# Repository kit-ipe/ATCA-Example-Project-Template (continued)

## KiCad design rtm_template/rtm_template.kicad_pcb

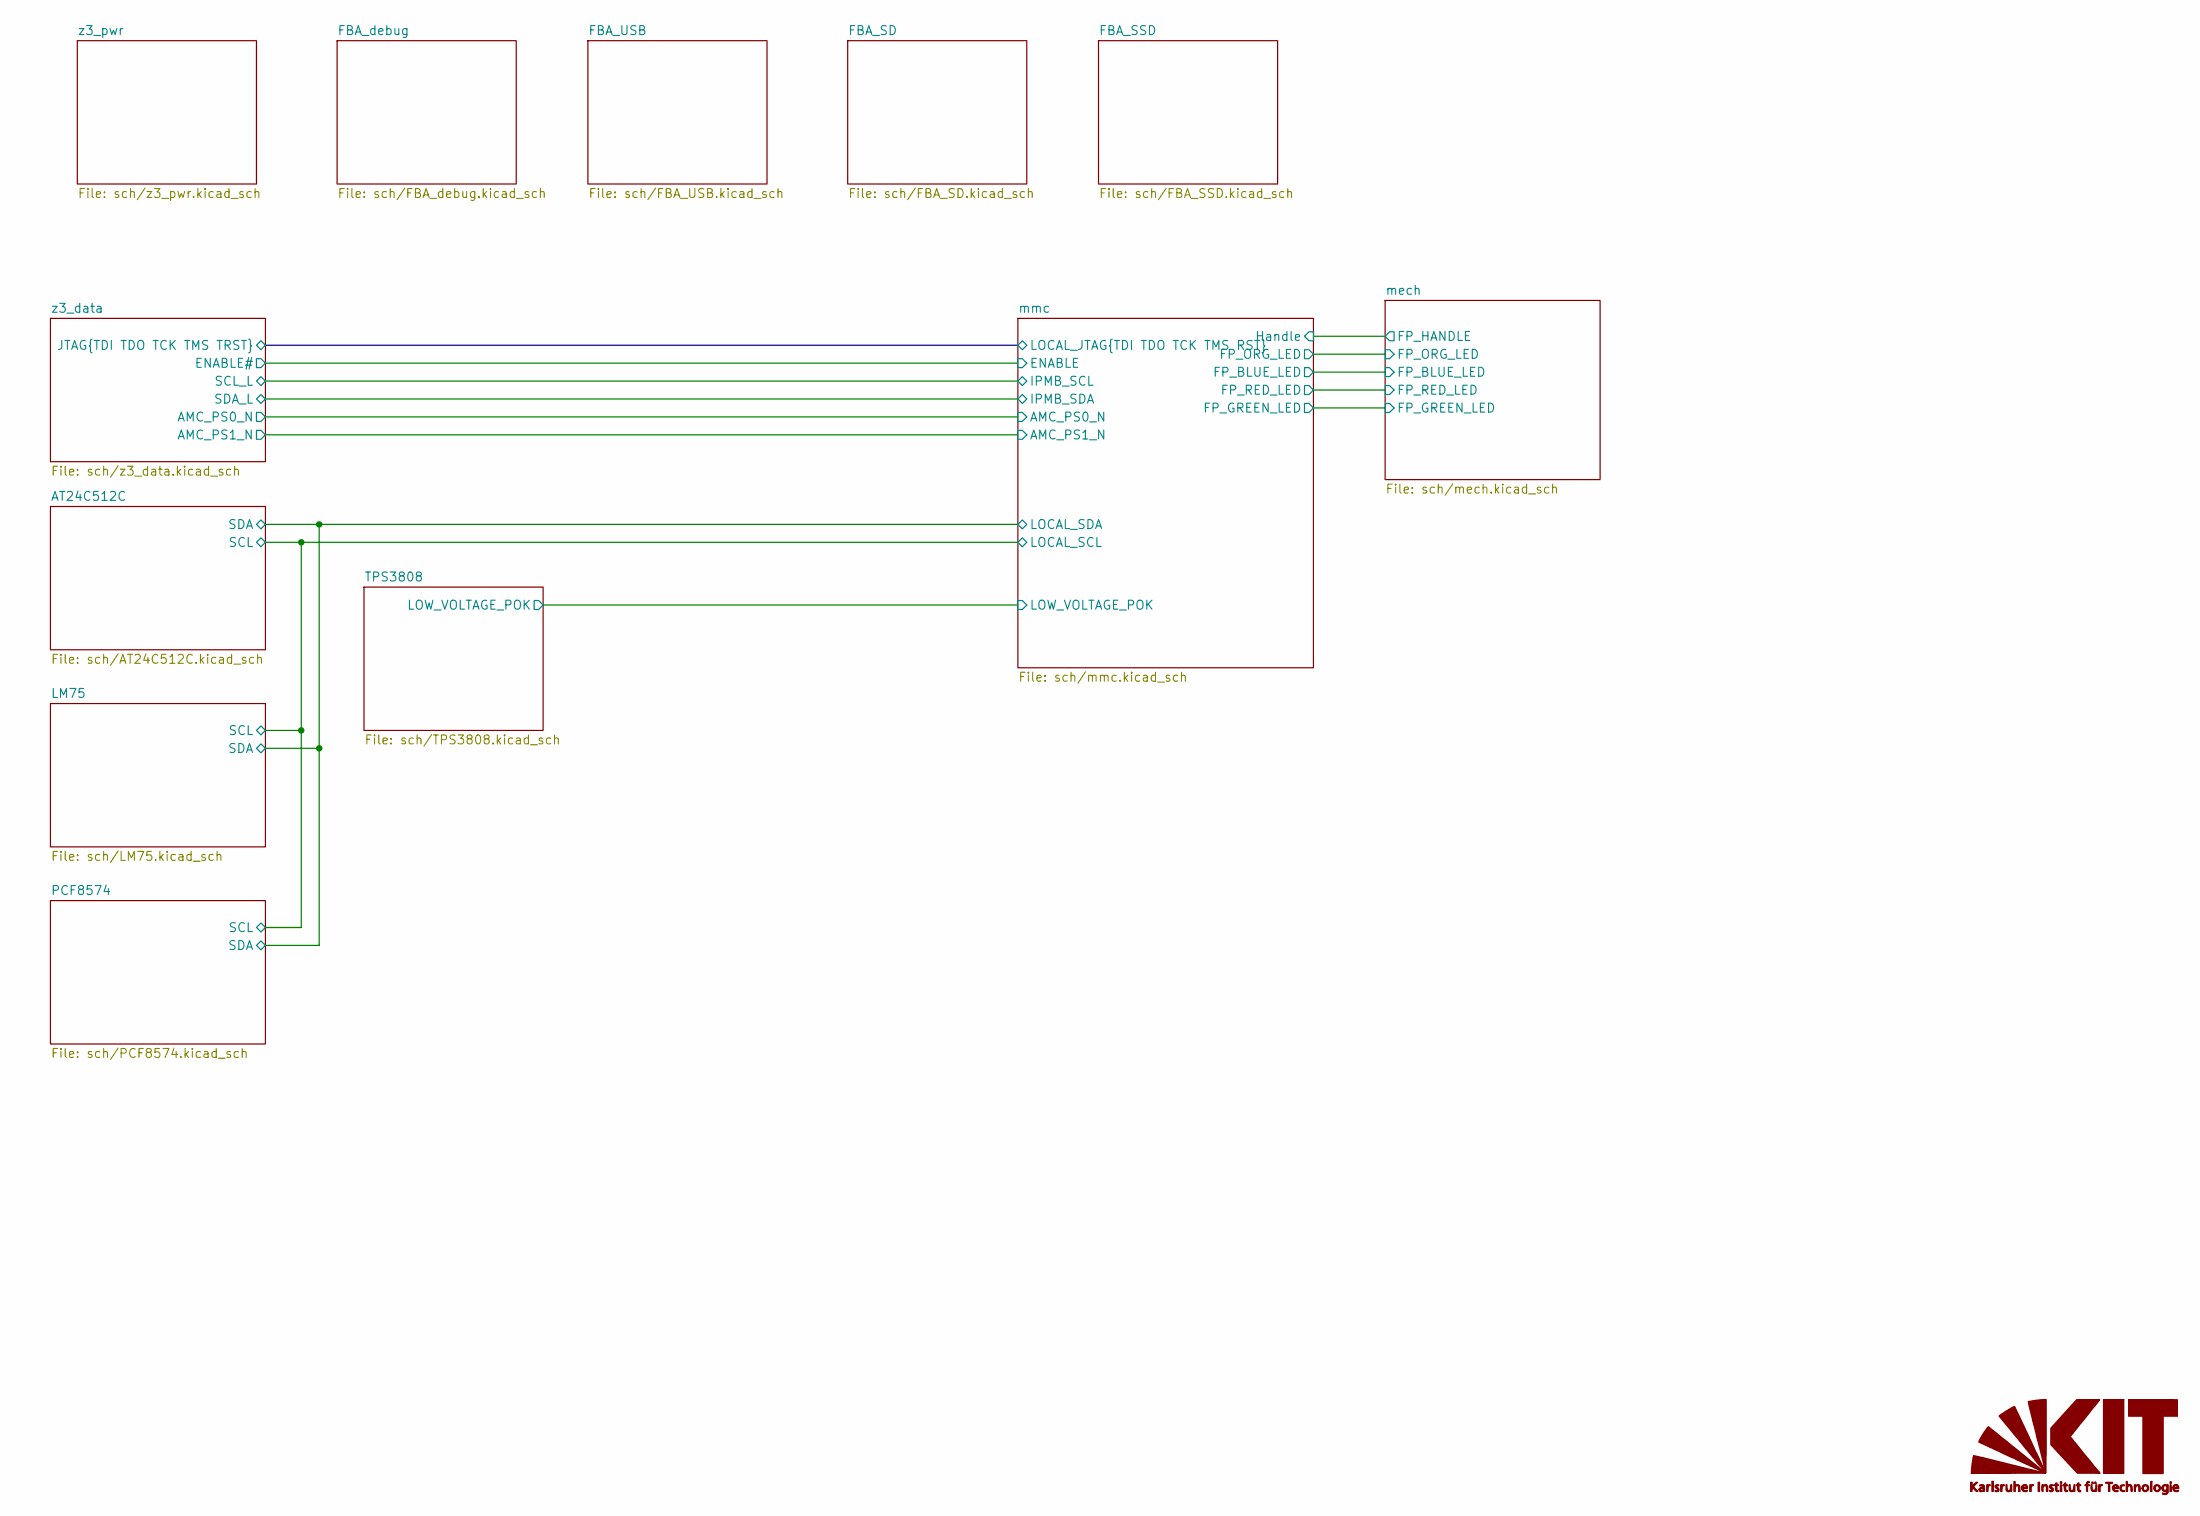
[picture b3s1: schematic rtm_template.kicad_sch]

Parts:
G1: KIT_LOGO

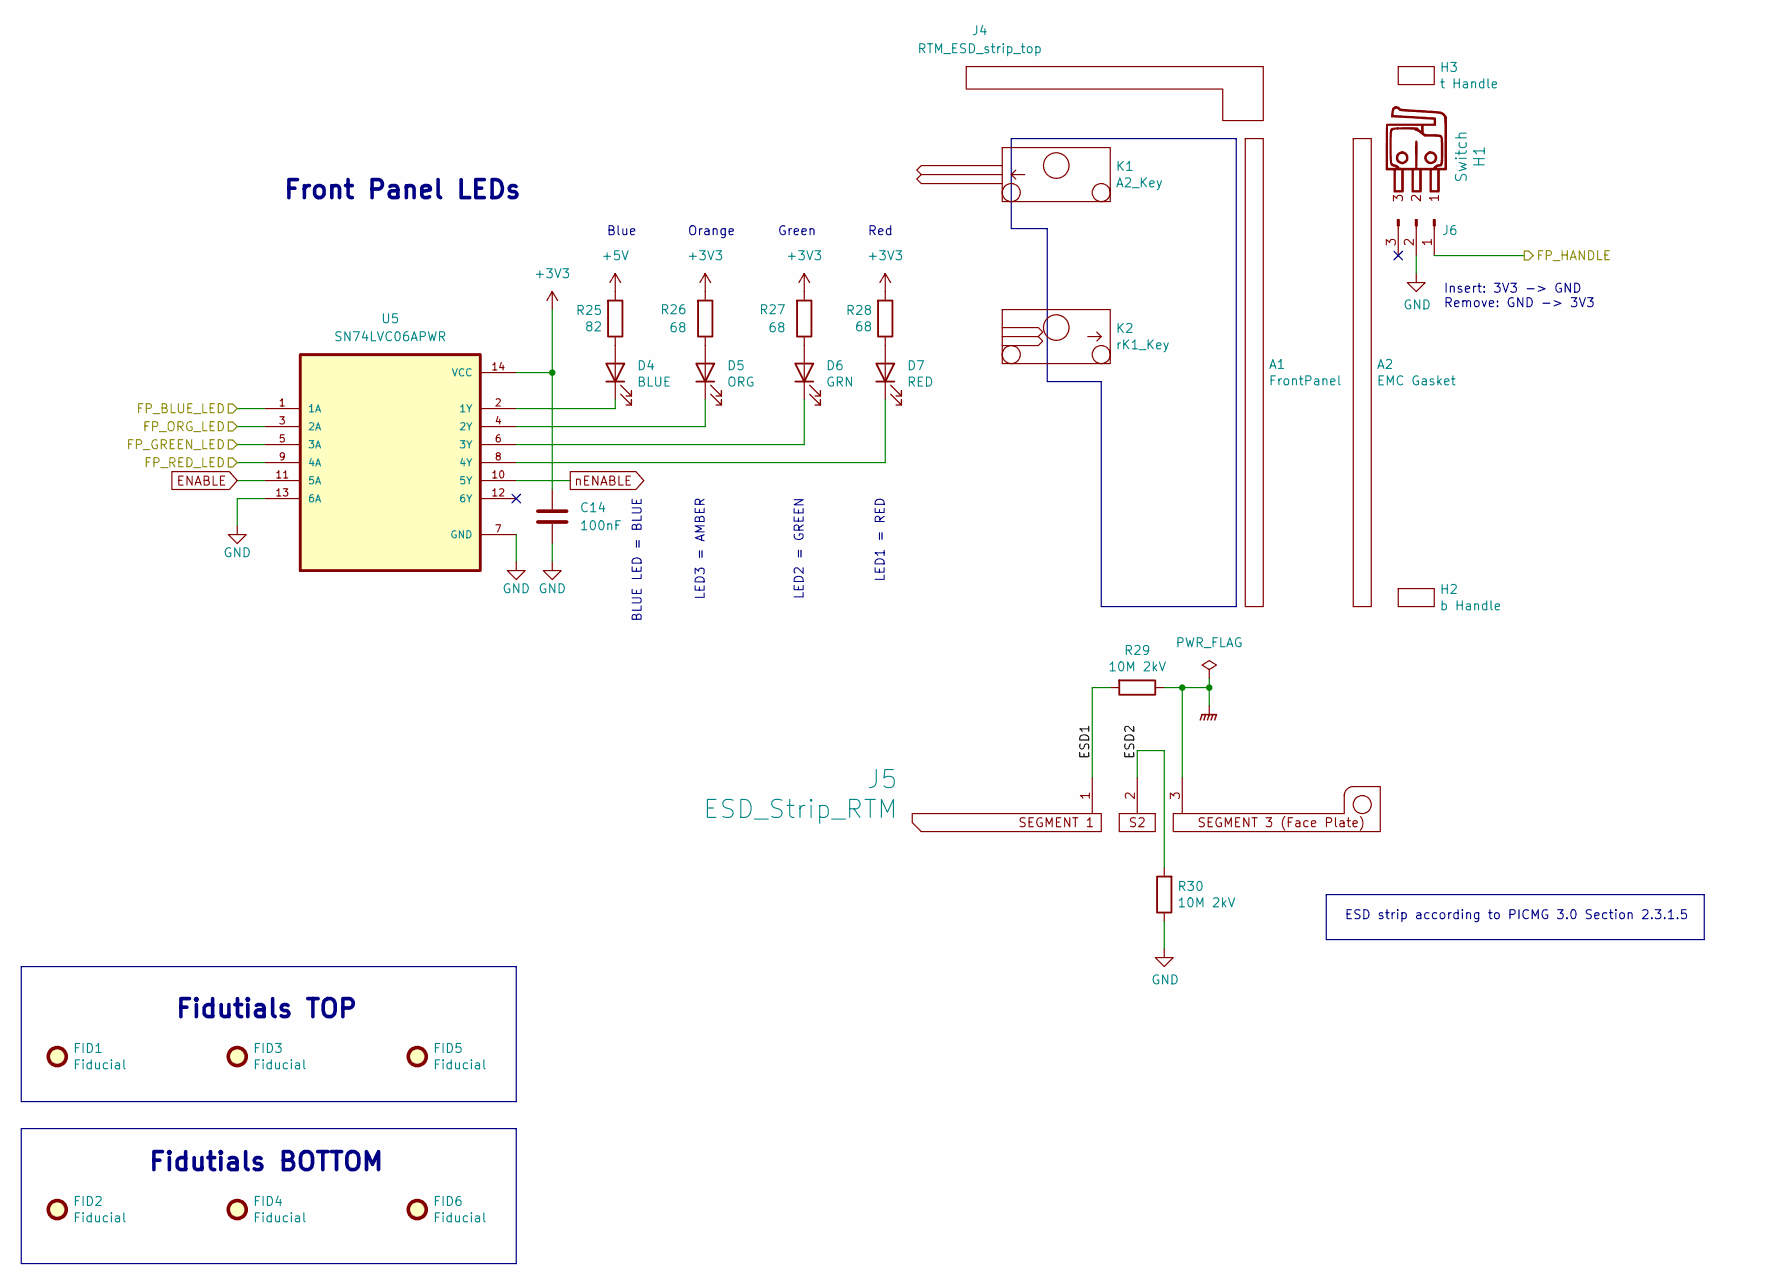
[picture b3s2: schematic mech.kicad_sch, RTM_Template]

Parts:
A1: FrontPanel
A2: EMC Gasket
C14: 100nF; C_0402_1005Metric
D4: BLUE; APA1606x; digikey# 754-1424-1-ND
D5: ORG; APA2106x; mouser# 604-APA2106SECK; digikey# 754-1059-1-ND
D6: GRN; APA2106x; digikey# 754-1057-1-ND
D7: RED; APA2106x; mouser# 604-APA2106SURCK; digikey# 754-1060-1-ND
FID1, FID2, FID3, FID4, FID5, FID6: Fiducial; Fiducial_1mm_Mask2mm
H1: Switch; 81-301-00
H2: b Handle; 81-300-00
H3: t Handle; 81-300-00
J4: RTM_ESD_strip_top
J5: ESD_Strip_RTM; RTM_ESD_strip_bottom
J6: Conn_01x03_Male; Molex_53046-0310; mouser# 538-53047-0310; digikey# WM1732-ND
K1: A2_Key; Key_A2_TE_1-1469372-1; mouser# 571-1-1469372-1; digikey# 1-1469372-1-ND
K2: rK1_Key; Key_rK1_TE_1469374-1; mouser# 571-1469374-1; digikey# A101978-ND
R25: 82; R_0402_1005Metric; digikey# A129614CT-ND
R26, R27, R28: 68; R_0402_1005Metric; digikey# A129613CT-ND
R29, R30: 10M 2kV; R_2010_5025Metric; digikey# 118-CHV2010-FX-1005ESTCT-ND
U5: SN74LVC06APWR; TSSOP-14_4.4x5mm_P0.65mm

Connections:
+3V3: C14.2, R26.2, R27.2, R28.2, U5.14 (VCC); also elsewhere on the board
+5V: R25.2; also elsewhere on the board
/mech/ESD1: J5.1, R29.2
/mech/ESD2: J5.2, R30.2
/mech/FP_BLUE_LED: U5.1 (1A); also elsewhere on the board
/mech/FP_GREEN_LED: U5.5 (3A); also elsewhere on the board
/mech/FP_HANDLE: J6.1; also elsewhere on the board
/mech/FP_ORG_LED: U5.3 (2A); also elsewhere on the board
/mech/FP_RED_LED: U5.9 (4A); also elsewhere on the board
ENABLE: U5.11 (5A); also elsewhere on the board
GND: C14.1, J6.2, R30.1, U5.7 (GND), U5.13 (6A); also elsewhere on the board
GNDPWR: J5.3, R29.1
unnamed: D4.1 (K), U5.2 (1Y)
unnamed: D4.2 (A), R25.1
unnamed: D5.1 (K), U5.4 (2Y)
unnamed: D5.2 (A), R26.1
unnamed: D6.1 (K), U5.6 (3Y)
unnamed: D6.2 (A), R27.1
unnamed: D7.1 (K), U5.8 (4Y)
unnamed: D7.2 (A), R28.1
nENABLE: U5.10 (5Y); also elsewhere on the board

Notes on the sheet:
LED2 = GREEN
LED1 = RED
Green
ESD strip according to PICMG 3.0 Section 2.3.1.5
Blue
LED3 = AMBER
Insert: 3V3 -> GND Remove: GND -> 3V3
Red
BLUE LED = BLUE
Fidutials BOTTOM
Fidutials TOP
Front Panel LEDs
Orange

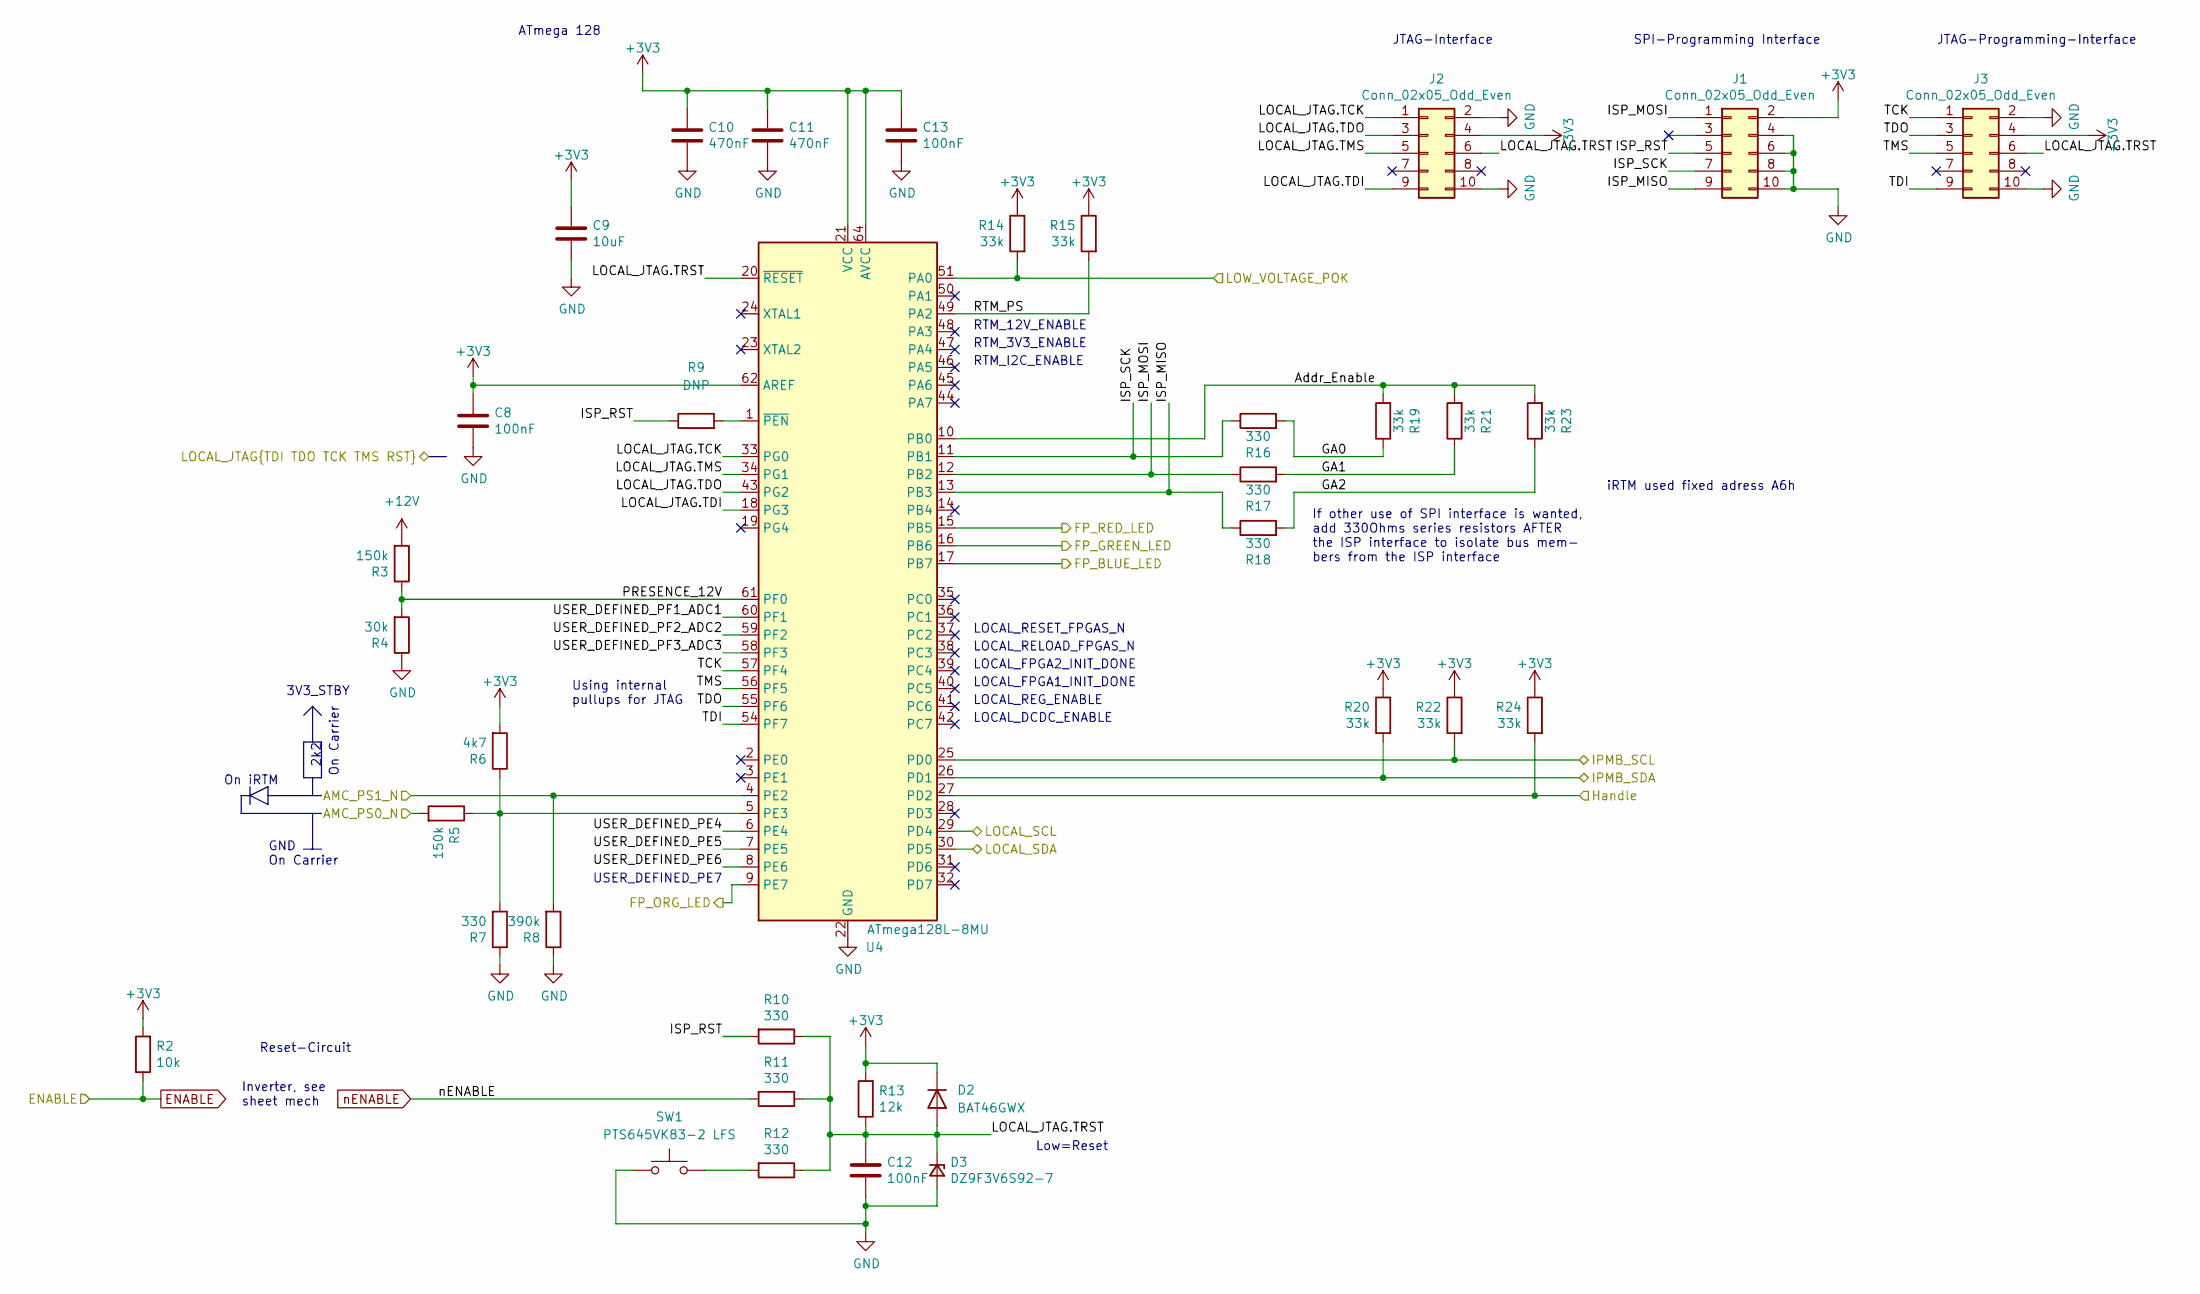
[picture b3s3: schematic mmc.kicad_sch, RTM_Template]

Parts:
C8, C12, C13: 100nF; C_0402_1005Metric
C9: 10uF; C_1210_3225Metric; digikey# 445-3942-1-ND
C10, C11: 470nF; C_0402_1005Metric
D2: BAT46GWX; D_SOD-123; mouser# 841-BAT46GWX
D3: DZ9F3V6S92-7; D_SOD-923; digikey# DZ9F3V6S92-7DICT-ND
J1: Conn_02x05_Odd_Even; PinHeader_2x05_P2.54mm_Vertical
J2, J3: Conn_02x05_Odd_Even; IDC-Header_2x05_P2.54mm_Horizontal_withoutsilkscreen; mouser# 571-5103311-1; digikey# A33180-ND
R2: 10k; R_0402_1005Metric; digikey# A129639CT-ND
R3, R5: 150k; R_0402_1005Metric
R4: 30k; R_0402_1005Metric
R6: 4k7; R_0402_1005Metric
R7, R10, R11, R12, R16, R17, R18: 330; R_0402_1005Metric
R8: 390k; R_0402_1005Metric
R9: DNP; R_0402_1005Metric
R13: 12k; R_0402_1005Metric
R14, R15, R19, R20, R21, R22, R23, R24: 33k; R_0402_1005Metric
SW1: PTS645VK83-2 LFS; PTS645VK83-2; digikey# CKN10950-ND
U4: ATmega128L-8MU; QFN-64-1EP_9x9mm_P0.5mm_EP5.4x5.4mm; mouser# 556-ATMEGA128L-8MUR; digikey# 2156-ATMEGA128L-8MU-ND

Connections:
+3V3: C8.1, C9.1, C10.2, C11.1, C13.1, D2.1 (K), J1.2, J2.4, J3.4, R2.2, R6.2, R13.2, R14.1, R15.1, R20.1, R22.1, R24.1, U4.21 (VCC), U4.52 (VCC), U4.62 (AREF), U4.64 (AVCC); also elsewhere on the board
+12V: R3.2; also elsewhere on the board
/AT24C512C/SCL: U4.29 (PD4); also elsewhere on the board
/AT24C512C/SDA: U4.30 (PD5); also elsewhere on the board
/TPS3808/LOW_VOLTAGE_POK: R14.2, U4.51 (PA0); also elsewhere on the board
/mech/FP_BLUE_LED: U4.17 (PB7); also elsewhere on the board
/mech/FP_GREEN_LED: U4.16 (PB6); also elsewhere on the board
/mech/FP_HANDLE: R24.2, U4.27 (PD2); also elsewhere on the board
/mech/FP_ORG_LED: U4.9 (PE7); also elsewhere on the board
/mech/FP_RED_LED: U4.15 (PB5); also elsewhere on the board
/mmc/AMC_PS0_N: R5.2; also elsewhere on the board
/mmc/AMC_PS1_N: R8.2, U4.4 (PE2); also elsewhere on the board
/mmc/Addr_Enable: R19.2, R21.2, R23.2, U4.10 (PB0)
/mmc/GA0: R16.2, R19.1
/mmc/GA1: R17.2, R21.1
/mmc/GA2: R18.2, R23.1
/mmc/IPMB_SCL: R22.2, U4.25 (PD0); also elsewhere on the board
/mmc/IPMB_SDA: R20.2, U4.26 (PD1); also elsewhere on the board
/mmc/ISP_MISO: J1.9, R18.1, U4.13 (PB3)
/mmc/ISP_MOSI: J1.1, R17.1, U4.12 (PB2)
/mmc/ISP_RST: J1.5, R9.1, R10.2
/mmc/ISP_SCK: J1.7, R16.1, U4.11 (PB1)
/mmc/LOCAL_JTAG.TRST: C12.1, D2.2 (A), D3.1 (K), J2.6, J3.6, R10.1, R11.1, R12.1, R13.1, U4.20 (~RESET)
/mmc/PRESENCE_12V: R3.1, R4.2, U4.61 (PF0)
/mmc/RTM_PS: R15.2, U4.49 (PA2)
/mmc/TCK: J3.1, U4.57 (PF4)
/mmc/TDI: J3.9, U4.54 (PF7)
/mmc/TDO: J3.3, U4.55 (PF6)
/mmc/TMS: J3.5, U4.56 (PF5)
/mmc/USER_DEFINED_PE4: U4.6 (PE4)
/mmc/USER_DEFINED_PE5: U4.7 (PE5)
/mmc/USER_DEFINED_PE6: U4.8 (PE6)
/mmc/USER_DEFINED_PF1_ADC1: U4.60 (PF1)
/mmc/USER_DEFINED_PF2_ADC2: U4.59 (PF2)
/mmc/USER_DEFINED_PF3_ADC3: U4.58 (PF3)
/z3_data/JTAG.TCK: J2.1, U4.33 (PG0); also elsewhere on the board
/z3_data/JTAG.TDI: J2.9, U4.18 (PG3); also elsewhere on the board
/z3_data/JTAG.TDO: J2.3, U4.43 (PG2); also elsewhere on the board
/z3_data/JTAG.TMS: J2.5, U4.34 (PG1); also elsewhere on the board
ENABLE: R2.1; also elsewhere on the board
GND: C8.2, C9.2, C10.1, C11.2, C12.2, C13.2, D3.2 (A), J1.4, J1.6, J1.8, J1.10, J2.2, J2.10, J3.2, J3.10, R4.1, R7.1, R8.1, SW1.1, U4.22 (GND), U4.53 (GND), U4.63 (GND), U4.65 (GND); also elsewhere on the board
unnamed: R5.1, R6.1, R7.2, U4.5 (PE3)
unnamed: R9.2, U4.1 (~PEN)
unnamed: R12.2, SW1.2
nENABLE: R11.2; also elsewhere on the board

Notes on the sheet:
If other use of SPI interface is wanted, add 330Ohms series resistors AFTER the ISP interface to isolate bus mem- bers from the ISP interface
LOCAL_REG_ENABLE
On iRTM
Inverter, see sheet mech
GND On Carrier
RTM_3V3_ENABLE
RTM_12V_ENABLE
LOCAL_RELOAD_FPGAS_N
SPI-Programming Interface
USER_DEFINED_PE7
JTAG-Programming-Interface
RTM_I2C_ENABLE
3V3_STBY
LOCAL_FPGA1_INIT_DONE
LOCAL_DCDC_ENABLE
On Carrier
Using internal pullups for JTAG
JTAG-Interface
ATmega 128
iRTM used fixed adress A6h
LOCAL_FPGA2_INIT_DONE
LOCAL_RESET_FPGAS_N
Reset-Circuit
Low=Reset
2k2

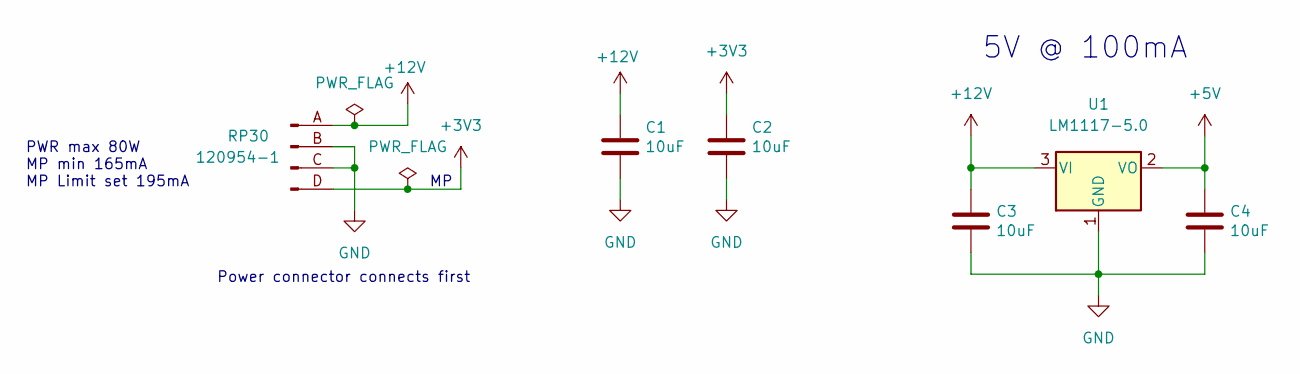
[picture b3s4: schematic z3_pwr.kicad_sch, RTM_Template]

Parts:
C1, C2, C3, C4: 10uF; C_1210_3225Metric; digikey# 445-3942-1-ND
RP30: 120954-1; mouser# 571-120954-1; digikey# A101829-ND
U1: LM1117-5.0; SOT-223-3_TabPin2; mouser# 863-LM1117MPX-50NOPB; digikey# 488-LM1117MPX-50NOPBCT-ND

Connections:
+3V3: C2.1, RP30.D; also elsewhere on the board
+5V: C4.1, U1.2 (VO); also elsewhere on the board
+12V: C1.1, C3.1, RP30.A, U1.3 (VI); also elsewhere on the board
GND: C1.2, C2.2, C3.2, C4.2, RP30.B, RP30.C, U1.1 (GND); also elsewhere on the board

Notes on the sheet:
Power connector connects first
PWR max 80W MP min 165mA MP Limit set 195mA
5V @ 100mA

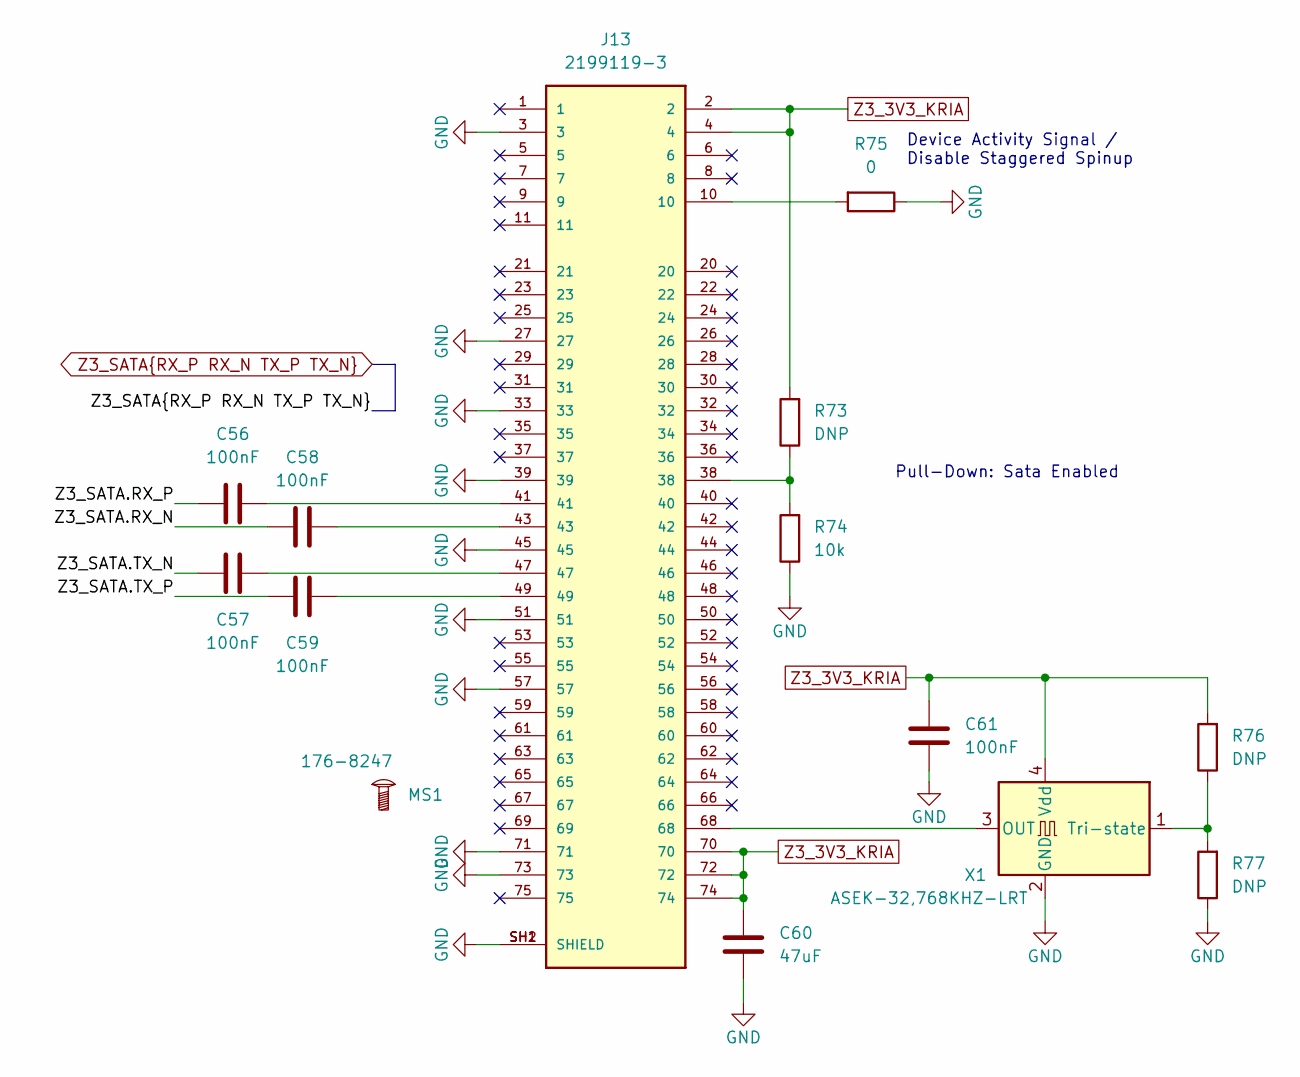
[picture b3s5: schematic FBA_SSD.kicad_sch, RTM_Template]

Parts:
C56, C57, C58, C59, C61: 100nF; C_0402_1005Metric; voltage 16 V
C60: 47uF; C_1210_3225Metric; digikey# 587-5924-1-ND
J13: 2199119-3; M.2_Type_B_2280; mouser# 571-2199119-3; digikey# A115899CT-ND
MS1: 176-8247
R73, R76, R77: DNP; R_0402_1005Metric_DNP
R74: 10k; R_0402_1005Metric; digikey# A129639CT-ND
R75: 0; R_0402_1005Metric
X1: ASEK-32,768KHZ-LRT; Oscillator_SMD_Abracon_ASE-4Pin_3.2x2.5mm; mouser# 815-ASEK-32.7K-LRT; digikey# 535-ASEK-32.768KHZ-L-R-TCT-ND

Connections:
GND: C60.2, C61.1, J13.3, J13.27, J13.33, J13.39, J13.45, J13.51, J13.57, J13.71, J13.73, J13.SH1 (SHIELD), J13.SH2 (SHIELD), R74.1, R75.1, R77.1, X1.2 (GND); also elsewhere on the board
unnamed: C56.2, J13.41
unnamed: C57.2, J13.47
unnamed: C58.2, J13.43
unnamed: C59.2, J13.49
unnamed: J13.10, R75.2
unnamed: J13.38, R73.1, R74.2
unnamed: J13.68, X1.3 (OUT)
unnamed: R76.1, R77.2, X1.1 (Tri-state)
Z3_3V3_KRIA: C60.1, C61.2, J13.2, J13.4, J13.70, J13.72, J13.74, R73.2, R76.2, X1.4 (Vdd); also elsewhere on the board
Z3_SATA.RX_N: C58.1; also elsewhere on the board
Z3_SATA.RX_P: C56.1; also elsewhere on the board
Z3_SATA.TX_N: C57.1; also elsewhere on the board
Z3_SATA.TX_P: C59.1; also elsewhere on the board

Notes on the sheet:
Device Activity Signal / Disable Staggered Spinup
Pull-Down: Sata Enabled

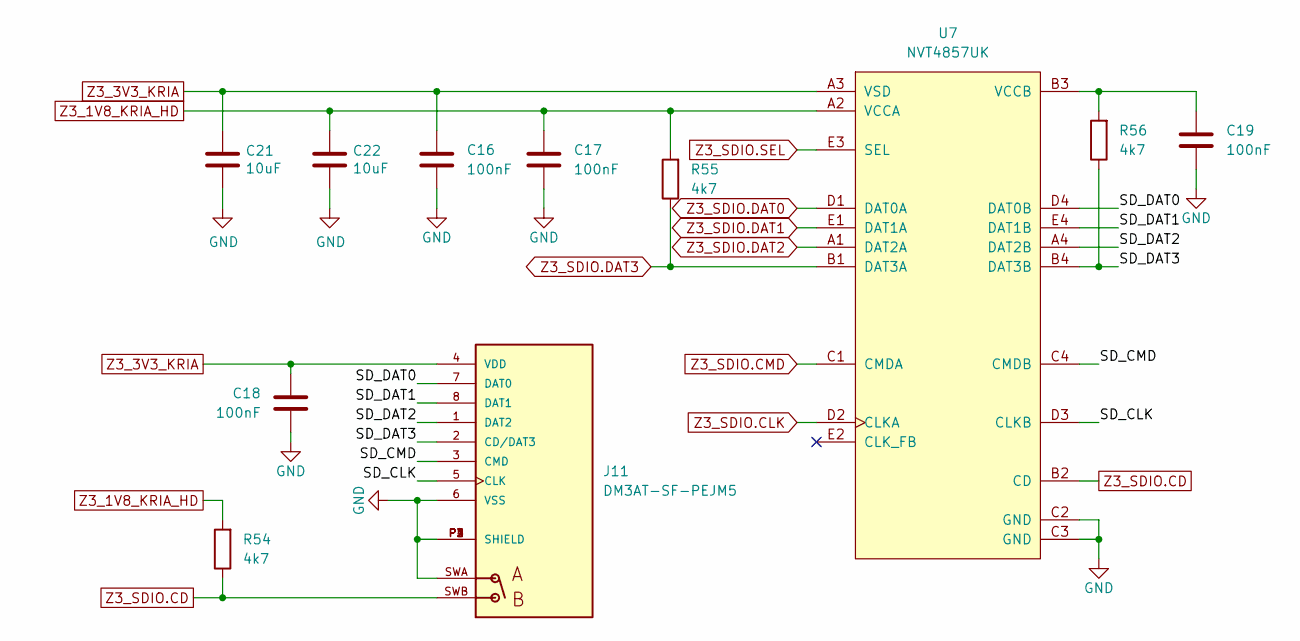
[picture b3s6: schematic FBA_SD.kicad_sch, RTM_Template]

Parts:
C16, C17, C18, C19: 100nF; C_0402_1005Metric; voltage 16 V
C21, C22: 10uF; C_1210_3225Metric; digikey# 445-3942-1-ND
J11: DM3AT-SF-PEJM5; mouser# 798-DM3AT-SF-PEJM5; digikey# HR1964CT-ND
R54, R55, R56: 4k7; R_0402_1005Metric; digikey# A129635CT-ND
U7: NVT4857UK; WLCSP-20_1.934x2.434mm_Layout4x5_P0.4mm; mouser# 771-NVT4857UKAZ; digikey# 568-15389-1-ND

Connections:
/FBA_SD/SD_CLK: J11.5 (CLK), U7.D3 (CLKB)
/FBA_SD/SD_CMD: J11.3 (CMD), U7.C4 (CMDB)
/FBA_SD/SD_DAT0: J11.7 (DAT0), U7.D4 (DAT0B)
/FBA_SD/SD_DAT1: J11.8 (DAT1), U7.E4 (DAT1B)
/FBA_SD/SD_DAT2: J11.1 (DAT2), U7.A4 (DAT2B)
/FBA_SD/SD_DAT3: J11.2 (CD/DAT3), R56.1, U7.B4 (DAT3B)
GND: C16.1, C17.1, C18.1, C19.1, C21.2, C22.2, J11.6 (VSS), J11.P1 (SHIELD), J11.P2 (SHIELD), J11.P3 (SHIELD), J11.P4 (SHIELD), J11.SWA, U7.C2 (GND), U7.C3 (GND); also elsewhere on the board
unnamed: C19.2, R56.2, U7.B3 (VCCB)
Z3_1V8_KRIA_HD: C17.2, C22.1, R54.2, R55.2, U7.A2 (VCCA); also elsewhere on the board
Z3_3V3_KRIA: C16.2, C18.2, C21.1, J11.4 (VDD), U7.A3 (VSD); also elsewhere on the board
Z3_SDIO.CD: J11.SWB, R54.1, U7.B2 (CD); also elsewhere on the board
Z3_SDIO.CLK: U7.D2 (CLKA); also elsewhere on the board
Z3_SDIO.CMD: U7.C1 (CMDA); also elsewhere on the board
Z3_SDIO.DAT0: U7.D1 (DAT0A); also elsewhere on the board
Z3_SDIO.DAT1: U7.E1 (DAT1A); also elsewhere on the board
Z3_SDIO.DAT2: U7.A1 (DAT2A); also elsewhere on the board
Z3_SDIO.DAT3: R55.1, U7.B1 (DAT3A); also elsewhere on the board
Z3_SDIO.SEL: U7.E3 (SEL); also elsewhere on the board

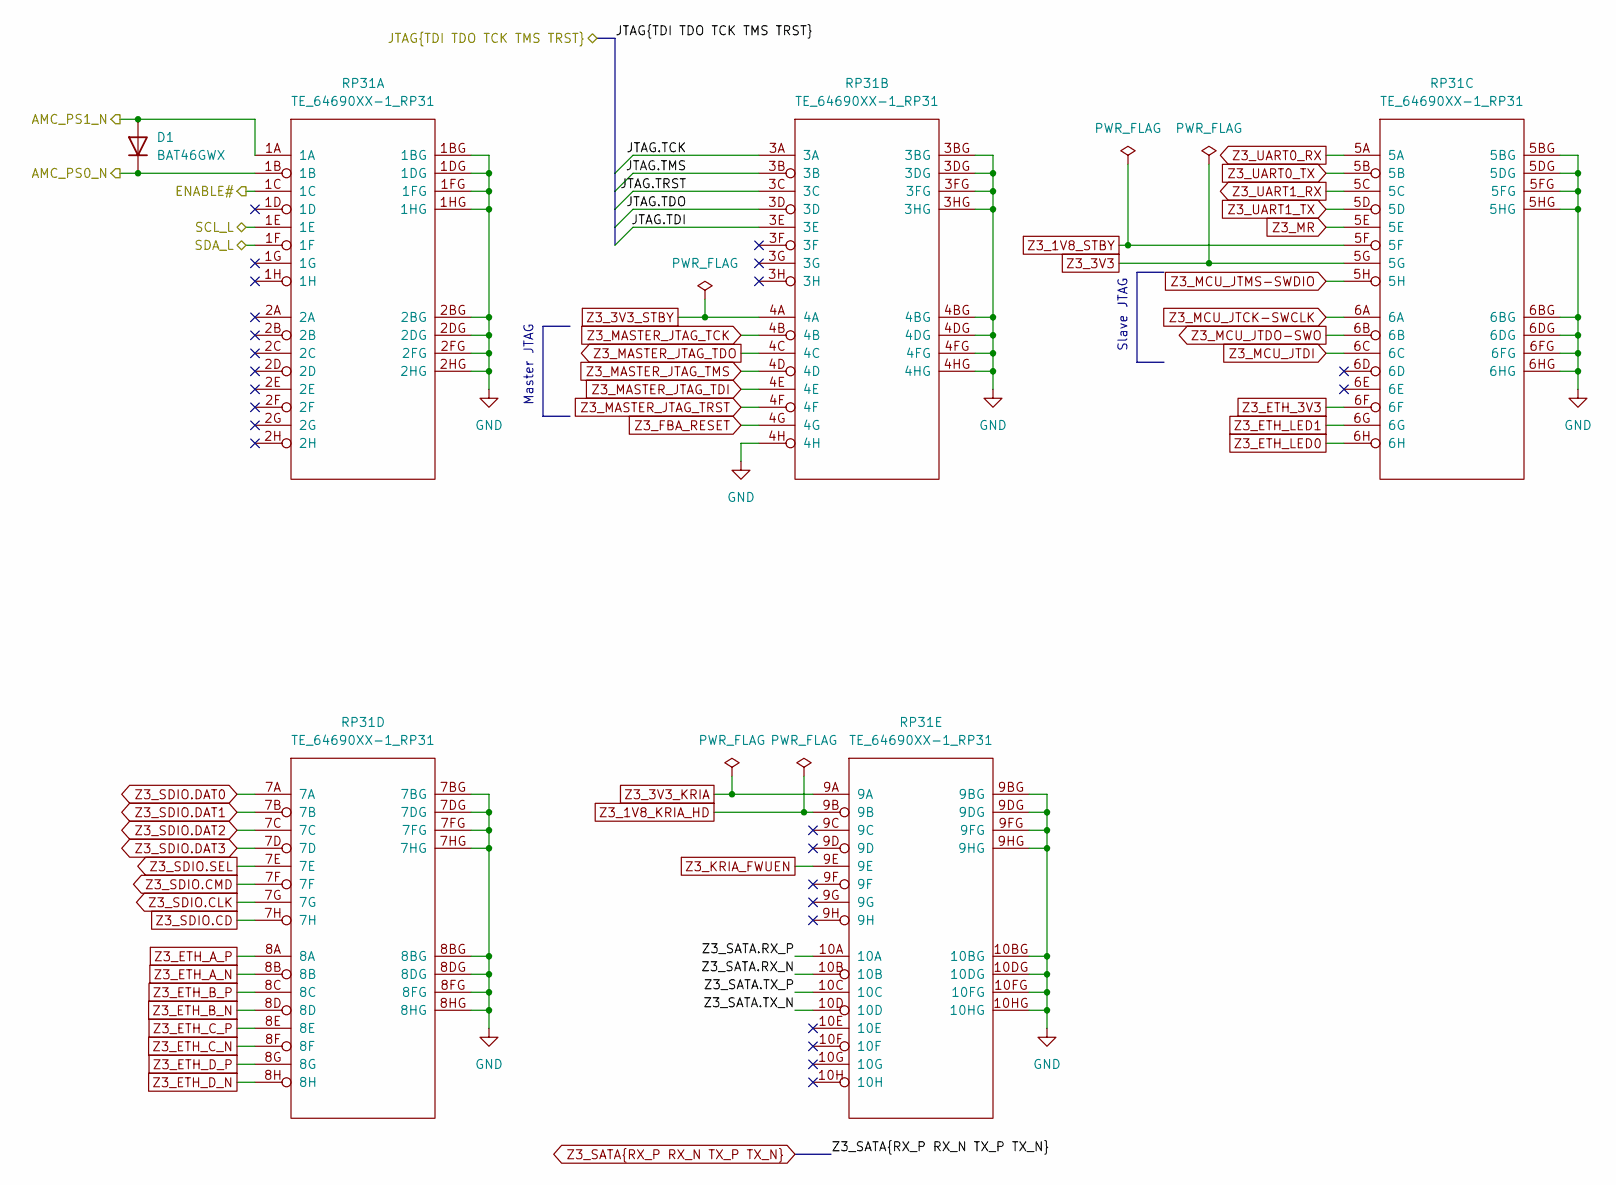
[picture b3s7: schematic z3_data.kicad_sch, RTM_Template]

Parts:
D1: BAT46GWX; D_SOD-123; mouser# 841-BAT46GWX
RP31: TE_64690XX-1_RP31; 6469048-1; mouser# 571-6469048-1; digikey# A115603-ND

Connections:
/mmc/AMC_PS0_N: D1.1 (K), RP31.1B; also elsewhere on the board
/mmc/AMC_PS1_N: D1.2 (A), RP31.1A; also elsewhere on the board
/mmc/IPMB_SCL: RP31.1E; also elsewhere on the board
/mmc/IPMB_SDA: RP31.1F; also elsewhere on the board
/z3_data/JTAG.TCK: RP31.3A; also elsewhere on the board
/z3_data/JTAG.TDI: RP31.3E; also elsewhere on the board
/z3_data/JTAG.TDO: RP31.3D; also elsewhere on the board
/z3_data/JTAG.TMS: RP31.3B; also elsewhere on the board
/z3_data/JTAG.TRST: RP31.3C
ENABLE: RP31.1C; also elsewhere on the board
GND: RP31.1BG, RP31.1DG, RP31.1FG, RP31.1HG, RP31.2BG, RP31.2DG, RP31.2FG, RP31.2HG, RP31.3BG, RP31.3DG, RP31.3FG, RP31.3HG, RP31.4BG, RP31.4DG, RP31.4FG, RP31.4H, RP31.4HG, RP31.5BG, RP31.5DG, RP31.5FG, RP31.5HG, RP31.6BG, RP31.6DG, RP31.6FG, RP31.6HG, RP31.7BG, RP31.7DG, RP31.7FG, RP31.7HG, RP31.8BG, RP31.8DG, RP31.8FG, RP31.8HG, RP31.9BG, RP31.9DG, RP31.9FG, RP31.9HG, RP31.10BG, RP31.10DG, RP31.10FG, RP31.10HG; also elsewhere on the board
Z3_1V8_KRIA_HD: RP31.9B; also elsewhere on the board
Z3_1V8_STBY: RP31.5F; also elsewhere on the board
Z3_3V3: RP31.5G; also elsewhere on the board
Z3_3V3_KRIA: RP31.9A; also elsewhere on the board
Z3_3V3_STBY: RP31.4A; also elsewhere on the board
Z3_ETH_3V3: RP31.6F; also elsewhere on the board
Z3_ETH_A_N: RP31.8B; also elsewhere on the board
Z3_ETH_A_P: RP31.8A; also elsewhere on the board
Z3_ETH_B_N: RP31.8D; also elsewhere on the board
Z3_ETH_B_P: RP31.8C; also elsewhere on the board
Z3_ETH_C_N: RP31.8F; also elsewhere on the board
Z3_ETH_C_P: RP31.8E; also elsewhere on the board
Z3_ETH_D_N: RP31.8H; also elsewhere on the board
Z3_ETH_D_P: RP31.8G; also elsewhere on the board
Z3_ETH_LED0: RP31.6H; also elsewhere on the board
Z3_ETH_LED1: RP31.6G; also elsewhere on the board
Z3_FBA_RESET: RP31.4G; also elsewhere on the board
Z3_KRIA_FWUEN: RP31.9E; also elsewhere on the board
Z3_MASTER_JTAG_TCK: RP31.4B; also elsewhere on the board
Z3_MASTER_JTAG_TDI: RP31.4E; also elsewhere on the board
Z3_MASTER_JTAG_TDO: RP31.4C; also elsewhere on the board
Z3_MASTER_JTAG_TMS: RP31.4D; also elsewhere on the board
Z3_MASTER_JTAG_TRST: RP31.4F; also elsewhere on the board
Z3_MCU_JTCK-SWCLK: RP31.6A; also elsewhere on the board
Z3_MCU_JTDI: RP31.6C; also elsewhere on the board
Z3_MCU_JTDO-SWO: RP31.6B; also elsewhere on the board
Z3_MCU_JTMS-SWDIO: RP31.5H; also elsewhere on the board
Z3_MR: RP31.5E; also elsewhere on the board
Z3_SATA.RX_N: RP31.10B; also elsewhere on the board
Z3_SATA.RX_P: RP31.10A; also elsewhere on the board
Z3_SATA.TX_N: RP31.10D; also elsewhere on the board
Z3_SATA.TX_P: RP31.10C; also elsewhere on the board
Z3_SDIO.CD: RP31.7H; also elsewhere on the board
Z3_SDIO.CLK: RP31.7G; also elsewhere on the board
Z3_SDIO.CMD: RP31.7F; also elsewhere on the board
Z3_SDIO.DAT0: RP31.7A; also elsewhere on the board
Z3_SDIO.DAT1: RP31.7B; also elsewhere on the board
Z3_SDIO.DAT2: RP31.7C; also elsewhere on the board
Z3_SDIO.DAT3: RP31.7D; also elsewhere on the board
Z3_SDIO.SEL: RP31.7E; also elsewhere on the board
Z3_UART0_RX: RP31.5A; also elsewhere on the board
Z3_UART0_TX: RP31.5B; also elsewhere on the board
Z3_UART1_RX: RP31.5C; also elsewhere on the board
Z3_UART1_TX: RP31.5D; also elsewhere on the board

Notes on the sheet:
Master JTAG
Slave JTAG

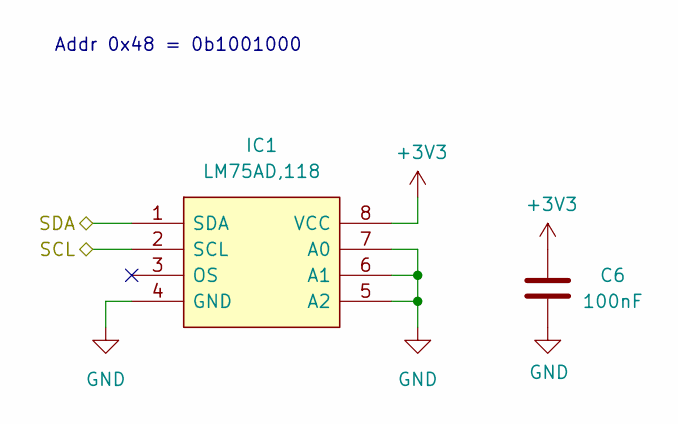
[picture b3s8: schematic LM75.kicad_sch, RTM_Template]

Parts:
C6: 100nF; C_0402_1005Metric
IC1: LM75AD,118; SO-8_3.9x4.9mm_P1.27mm; mouser# 771-LM75AD-T

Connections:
+3V3: C6.1, IC1.8 (VCC); also elsewhere on the board
/AT24C512C/SCL: IC1.2 (SCL); also elsewhere on the board
/AT24C512C/SDA: IC1.1 (SDA); also elsewhere on the board
GND: C6.2, IC1.4 (GND), IC1.5 (A2), IC1.6 (A1), IC1.7 (A0); also elsewhere on the board

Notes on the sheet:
Addr 0x48 = 0b1001000

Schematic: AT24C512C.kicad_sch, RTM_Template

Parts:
C7: 100nF; C_0402_1005Metric
U3: AT24C512C; DFN-8-1EP_3x2mm_P0.5mm_EP1.3x1.5mm; digikey# AT24C512C-MAHM-TCT-ND

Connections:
+3V3: C7.1, U3.8 (VCC); also elsewhere on the board
/AT24C512C/SCL: U3.6 (SCL); also elsewhere on the board
/AT24C512C/SDA: U3.5 (SDA); also elsewhere on the board
GND: C7.2, U3.1 (A0), U3.2 (A1), U3.3 (A2), U3.4 (GND), U3.7 (WP); also elsewhere on the board

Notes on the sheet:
I2C Address 8'hA0 -> 8'b1010_000(r/~{w}) 7'h50 -> 7'b101_0000
If the DRC gives an error because of the Thermal Pad, manually connect the pad in the Layout to GND
